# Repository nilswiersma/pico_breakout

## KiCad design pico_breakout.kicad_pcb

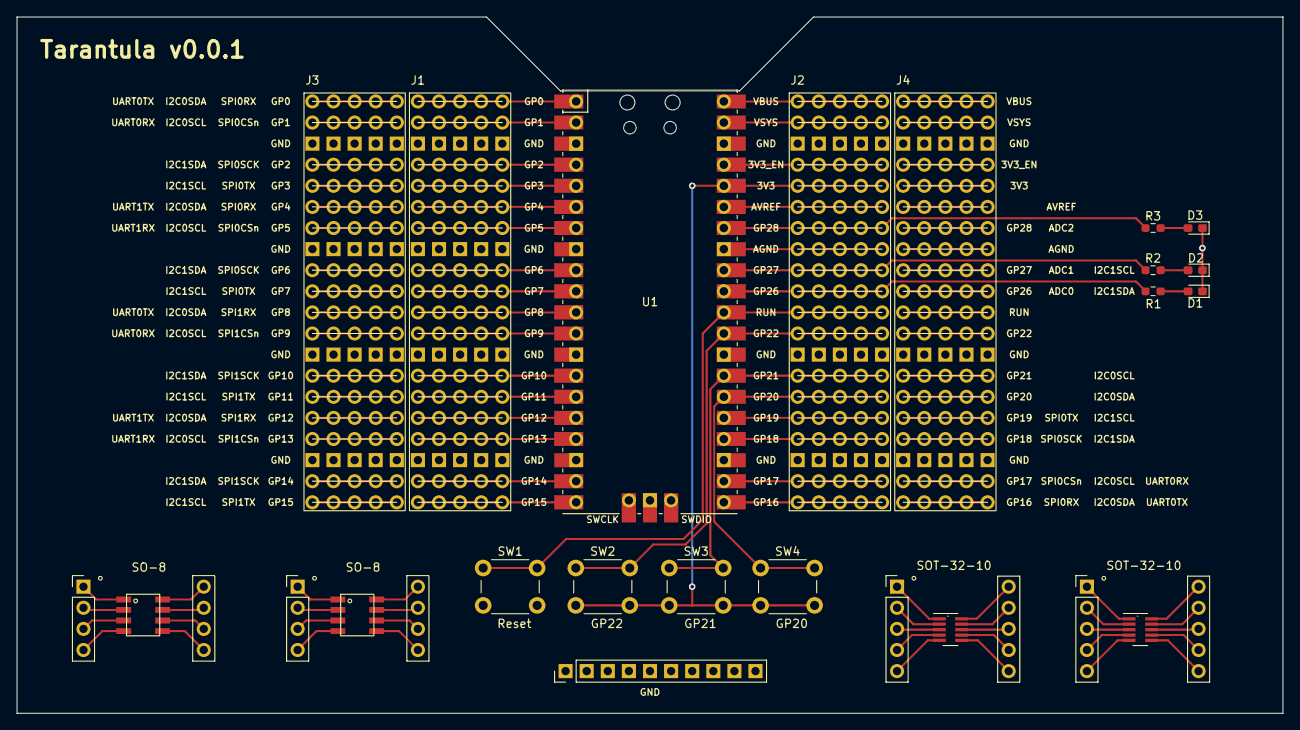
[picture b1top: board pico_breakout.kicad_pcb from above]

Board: 2 copper layers, 152.4 x 83.8 mm, 19 parts (0 on the bottom side), 37 nets.

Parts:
D1, D2, D3: LED; LED_0603_1608Metric_Pad1.05x0.95mm_HandSolder
J1, J2, J3, J4: Conn_05x20_Pin; PicoBreakout_5x20_P2.54mm_Vertical
R1, R2, R3: R; R_0603_1608Metric_Pad0.98x0.95mm_HandSolder
SO-8, SO-8#2: SO-8-breakout
SOT-32-10, SOT-32-10#2: SOT-32-10-breakout
SW1: Reset; SW_PUSH_6mm
SW2: GP22; SW_PUSH_6mm
SW3: GP21; SW_PUSH_6mm
SW4: GP20; SW_PUSH_6mm
U1: Pico; RPi_Pico_SMD_TH

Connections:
/3V3: J2.5, SW2.2, SW3.2, SW4.2, U1.36 (3V3)
/3V3_EN: J2.4, U1.37 (3V3_EN)
/ADC_VREF: J2.6, U1.35 (ADC_VREF)
/GPIO0: J1.1, U1.1 (GPIO0)
/GPIO1: J1.2, U1.2 (GPIO1)
/GPIO2: J1.4, U1.4 (GPIO2)
/GPIO3: J1.5, U1.5 (GPIO3)
/GPIO4: J1.6, U1.6 (GPIO4)
/GPIO5: J1.7, U1.7 (GPIO5)
/GPIO6: J1.9, U1.9 (GPIO6)
/GPIO7: J1.10, U1.10 (GPIO7)
/GPIO8: J1.11, U1.11 (GPIO8)
/GPIO9: J1.12, U1.12 (GPIO9)
/GPIO10: J1.14, U1.14 (GPIO10)
/GPIO11: J1.15, U1.15 (GPIO11)
/GPIO12: J1.16, U1.16 (GPIO12)
/GPIO13: J1.17, U1.17 (GPIO13)
/GPIO14: J1.19, U1.19 (GPIO14)
/GPIO15: J1.20, U1.20 (GPIO15)
/GPIO16: J2.20, U1.21 (GPIO16)
/GPIO17: J2.19, U1.22 (GPIO17)
/GPIO18: J2.17, U1.24 (GPIO18)
/GPIO19: J2.16, U1.25 (GPIO19)
/GPIO20: J2.15, SW4.1, U1.26 (GPIO20)
/GPIO21: J2.14, SW3.1, U1.27 (GPIO21)
/GPIO22: J2.12, SW2.1, U1.29 (GPIO22)
/GPIO26: J2.10, R1.1, U1.31 (GPIO26_ADC0)
/GPIO27: J2.9, R2.1, U1.32 (GPIO27_ADC1)
/GPIO28: J2.7, R3.1, U1.34 (GPIO28_ADC2)
/RUN: J2.11, SW1.1, U1.30 (RUN)
/VBUS: J2.1, U1.40 (VBUS)
/VSYS: J2.2, U1.39 (VSYS)
GND: D1.1 (K), D2.1 (K), D3.1 (K), J1.3, J1.8, J1.13, J1.18, J2.3, J2.13, J2.18, J3.3, J3.8, J3.13, J3.18, J4.3, J4.13, J4.18, SW1.2, U1.3 (GND), U1.8 (GND), U1.13 (GND), U1.18 (GND), U1.23 (GND), U1.28 (GND), U1.38 (GND), U1.42 (GND)
unnamed: D1.2 (A), R1.2
unnamed: D2.2 (A), R2.2
unnamed: D3.2 (A), R3.2
unnamed: J2.8, U1.33 (AGND)

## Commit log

2023-07-14 v0.0.1
2023-07-14 README.md
